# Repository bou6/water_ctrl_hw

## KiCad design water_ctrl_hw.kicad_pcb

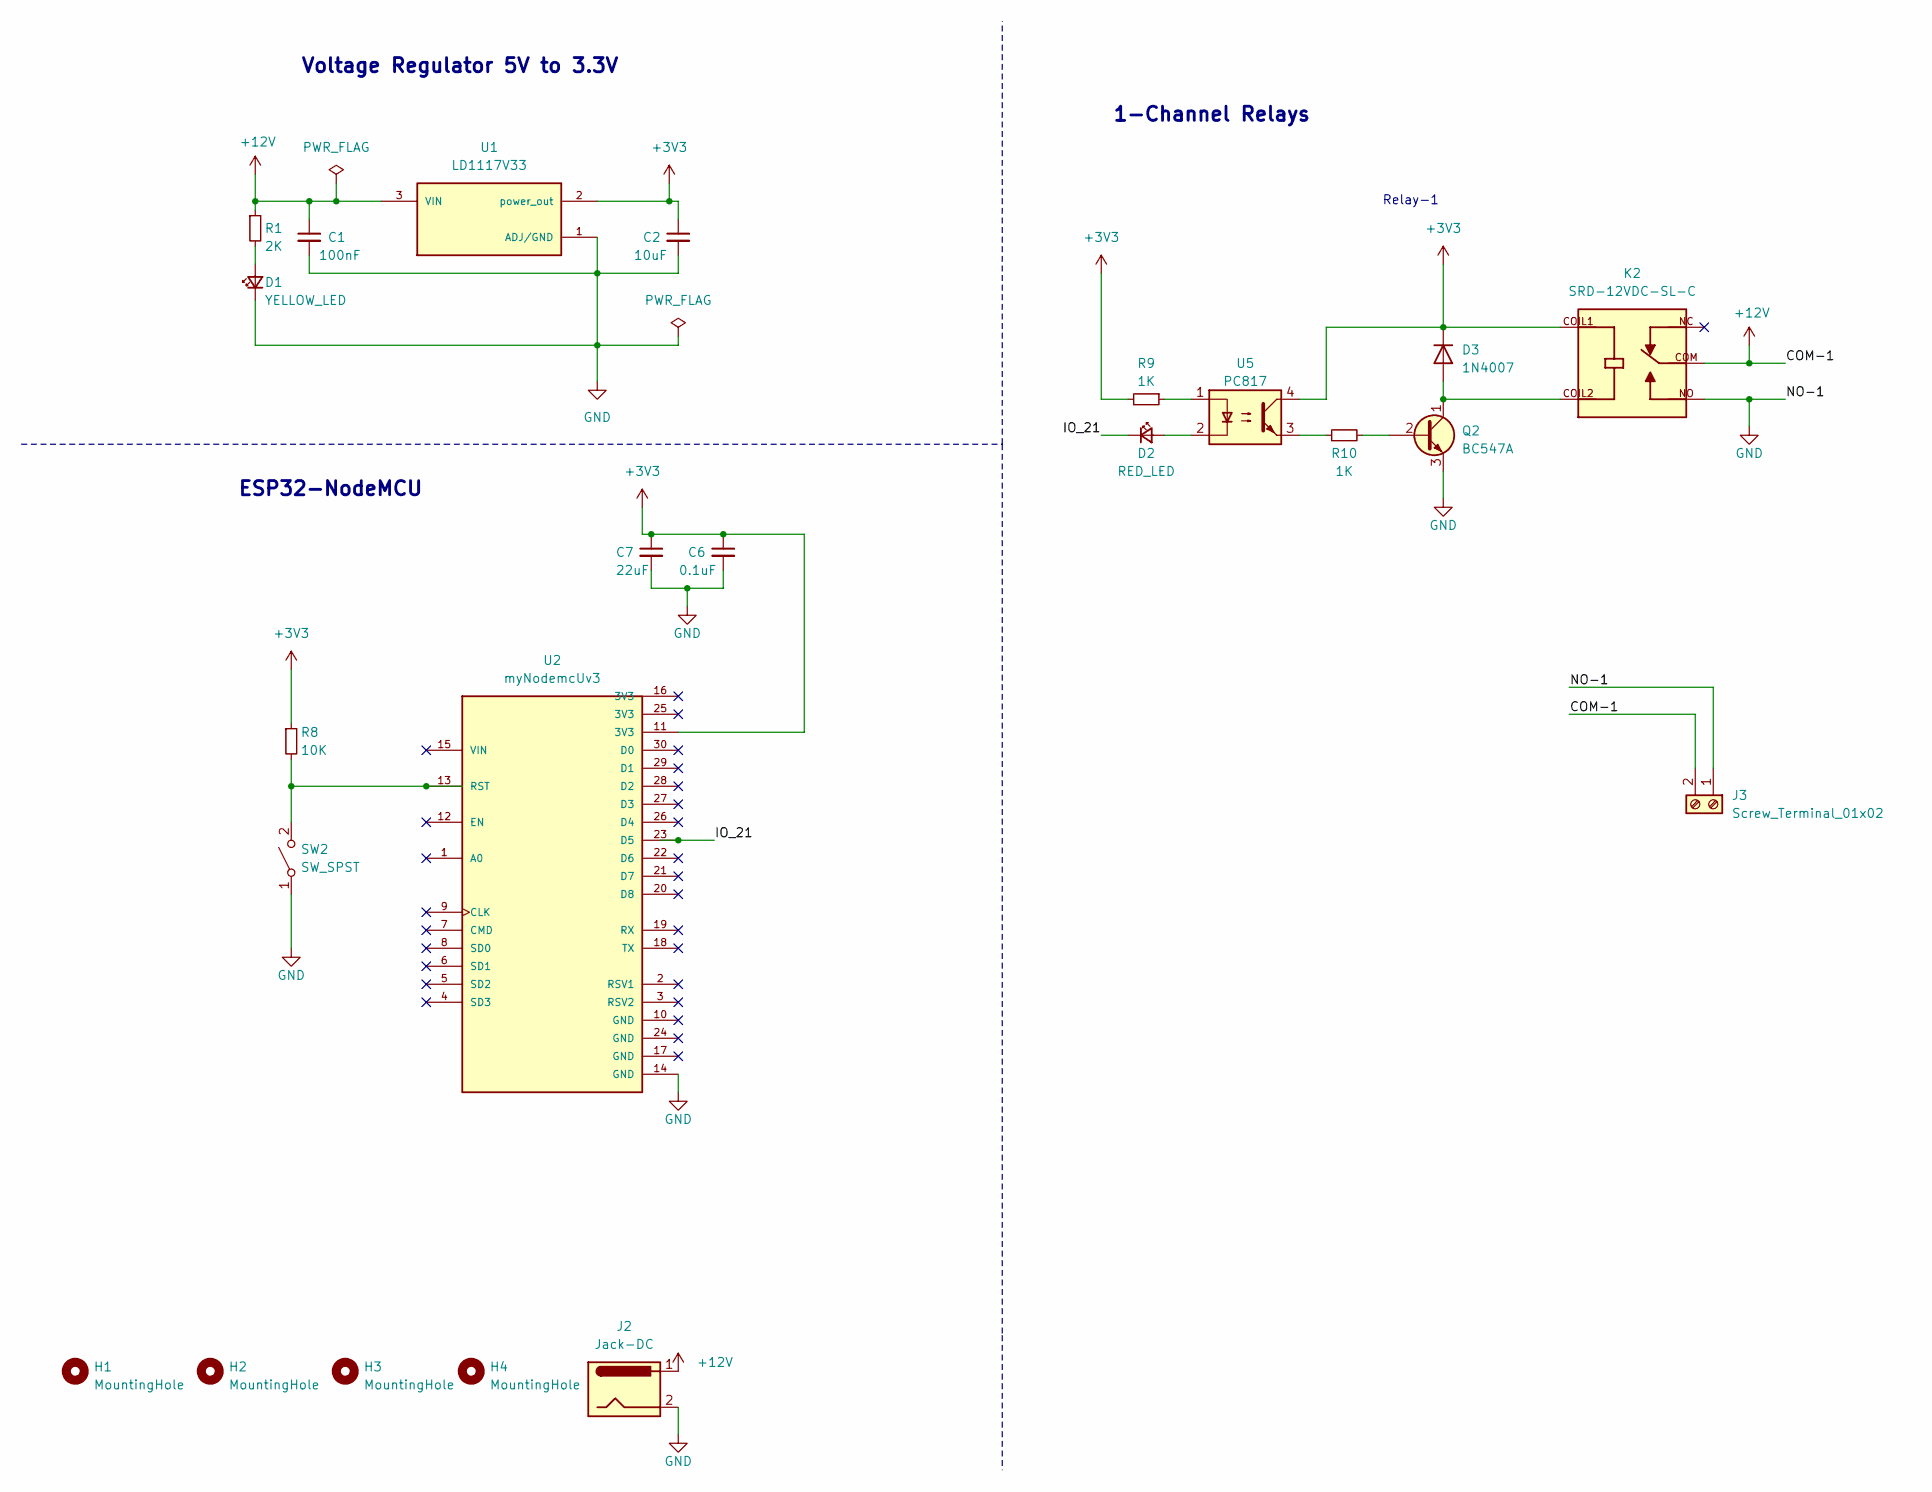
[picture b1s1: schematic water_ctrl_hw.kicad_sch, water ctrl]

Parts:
C1: 100nF; C_0805_2012Metric_Pad1.18x1.45mm_HandSolder
C2: 10uF; C_0805_2012Metric_Pad1.18x1.45mm_HandSolder
C6: 0.1uF; C_0805_2012Metric_Pad1.18x1.45mm_HandSolder
C7: 22uF; C_0805_2012Metric_Pad1.18x1.45mm_HandSolder
D1: YELLOW_LED; LED_0805_2012Metric_Pad1.15x1.40mm_HandSolder
D2: RED_LED; LED_0805_2012Metric_Pad1.15x1.40mm_HandSolder
D3: 1N4007; D_DO-41_SOD81_P10.16mm_Horizontal
H1, H2, H3, H4: MountingHole; MountingHole_3.2mm_M3
J2: Jack-DC; BarrelJack_CUI_PJ-063AH_Horizontal
J3: Screw_Terminal_01x02; TerminalBlock_Xinya_XY308-2.54-2P_1x02_P2.54mm_Horizontal
K2: SRD-12VDC-SL-C; RELAY_SRD-12VDC-SL-C; PARTREV 1.0
Q2: BC547A; TO-92_Inline
R1: 2K; R_0805_2012Metric_Pad1.20x1.40mm_HandSolder
R8: 10K; R_0805_2012Metric_Pad1.20x1.40mm_HandSolder
R9, R10: 1K; R_0805_2012Metric_Pad1.20x1.40mm_HandSolder
SW2: SW_SPST; SW_SPST_B3U-1000P
U1: LD1117V33; TO255P1020X450X1968-3; PARTREV 37
U2: myNodemcUv3; myNodeMcuv3; PARTREV 1.0
U5: PC817; DIP-4_W7.62mm

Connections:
+3V3: C2.1, C6.1, C7.1, D3.1 (K), K2.COIL1, R8.1, R9.2, U1.2 (power_out), U2.11 (3V3), U5.4
+12V: C1.1, J2.1, J3.2, K2.COM, R1.1, U1.3 (VIN)
/IO_21: D2.1 (K), U2.23 (D5)
GND: C1.2, C2.2, C6.2, C7.2, D1.1 (K), J2.2, J3.1, K2.NO, Q2.3 (E), SW2.1 (A), U1.1 (ADJ/GND), U2.14 (GND)
unnamed: D1.2 (A), R1.2
unnamed: D2.2 (A), U5.2
unnamed: D3.2 (A), K2.COIL2, Q2.1 (C)
unnamed: Q2.2 (B), R10.2
unnamed: R9.1, U5.1
unnamed: R10.1, U5.3
unnamed: R8.2, SW2.2 (B), U2.13 (RST)

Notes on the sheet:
Voltage Regulator 5V to 3.3V
1-Channel Relays
Relay-1
ESP32-NodeMCU

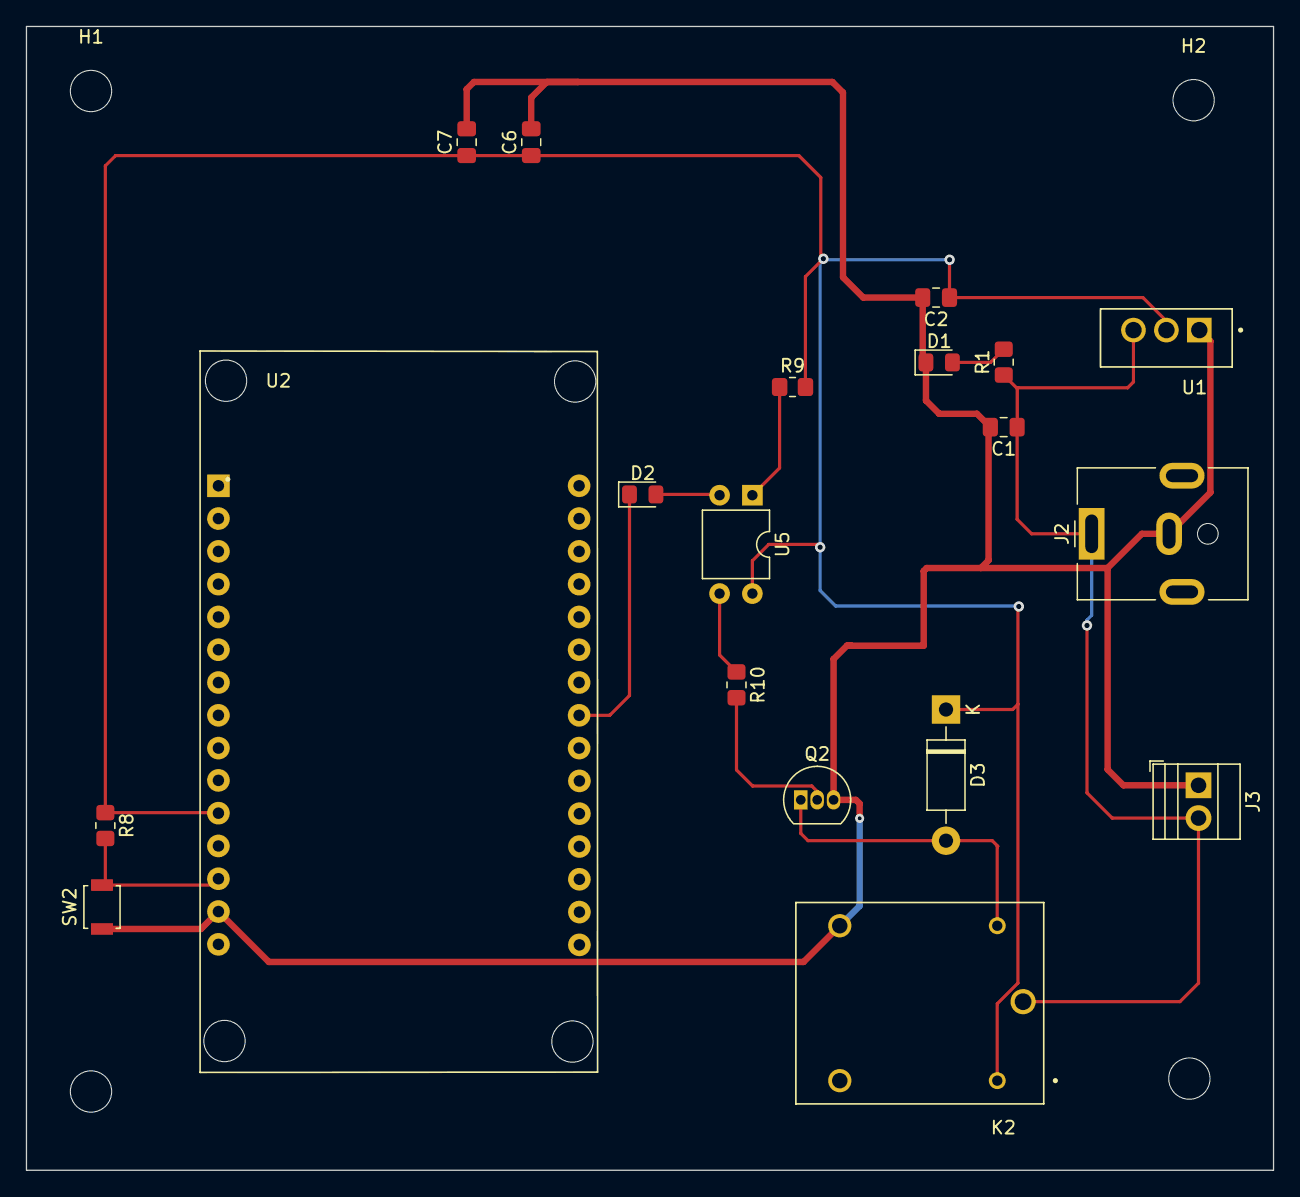
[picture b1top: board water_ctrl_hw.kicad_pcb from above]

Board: 2 copper layers, 96.6 x 88.6 mm, 23 parts (0 on the bottom side), 11 nets.

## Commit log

2024-10-10 1st commit
2024-10-10 remove uneeded files
2024-10-10 remove unneeded files
